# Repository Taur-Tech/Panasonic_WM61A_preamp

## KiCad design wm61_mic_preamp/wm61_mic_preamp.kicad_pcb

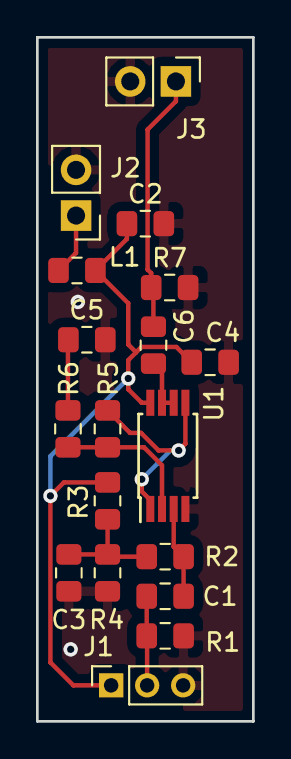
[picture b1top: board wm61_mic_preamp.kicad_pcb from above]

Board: 2 copper layers, 12.0 x 38.0 mm, 18 parts (0 on the bottom side), 11 nets.

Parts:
C1, C6: 2.2u; C_0805_2012Metric_Pad1.15x1.40mm_HandSolder
C2: 0.1u; C_0805_2012Metric_Pad1.15x1.40mm_HandSolder
C3, C5: 4.7u; C_0805_2012Metric_Pad1.15x1.40mm_HandSolder
C4: 10u; C_0805_2012Metric_Pad1.15x1.40mm_HandSolder
J1: WM60-WM61; PinSocket_1x03_P2.00mm_Vertical
J2: 5V; PinHeader_1x02_P2.54mm_Vertical
J3: Out; PinHeader_1x02_P2.54mm_Vertical
L1: Ferrite_Bead; L_0805_2012Metric_Pad1.15x1.40mm_HandSolder
R1, R2: 10k; R_0805_2012Metric_Pad1.15x1.40mm_HandSolder
R3, R4: 1k; R_0805_2012Metric_Pad1.15x1.40mm_HandSolder
R5: 15k; R_0805_2012Metric_Pad1.15x1.40mm_HandSolder
R6: 1k6; R_0805_2012Metric_Pad1.15x1.40mm_HandSolder
R7: 47k; R_0805_2012Metric_Pad1.15x1.40mm_HandSolder
U1: OPA2320; TSSOP-8_4.4x3mm_P0.65mm

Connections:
GND: C2.2, C3.2, C4.2, C5.2, J1.3, J2.2, J3.2, R1.2, R4.2, R7.2, U1.4
unnamed: C1.1, R2.2, U1.3
unnamed: C1.2, J1.2, R1.1
unnamed: C2.1, C4.1, J1.1, L1.2, R3.2, U1.8
unnamed: C3.1, R2.1, R3.1, R4.1
unnamed: C5.1, R6.2
unnamed: C6.1, J3.1, R7.1
unnamed: C6.2, U1.6, U1.7
unnamed: J2.1, L1.1
unnamed: R5.1, R6.1, U1.2
unnamed: R5.2, U1.1, U1.5

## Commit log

2019-08-24 :circus_tent: Added .gitattributes & .gitignore files
2019-08-24 rev 0 design commit
2019-09-21 changed opamp
